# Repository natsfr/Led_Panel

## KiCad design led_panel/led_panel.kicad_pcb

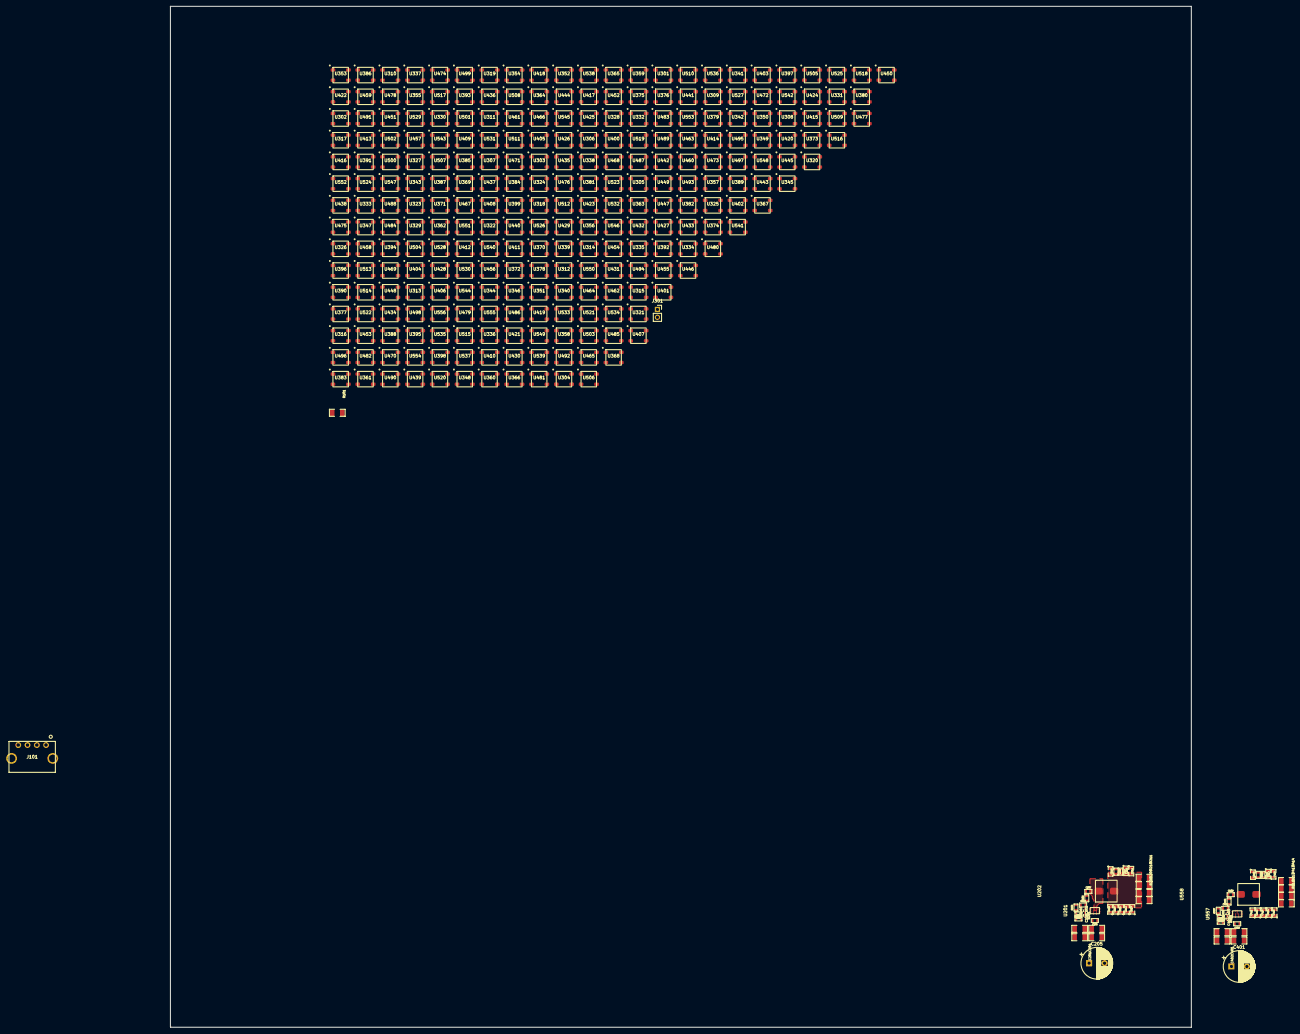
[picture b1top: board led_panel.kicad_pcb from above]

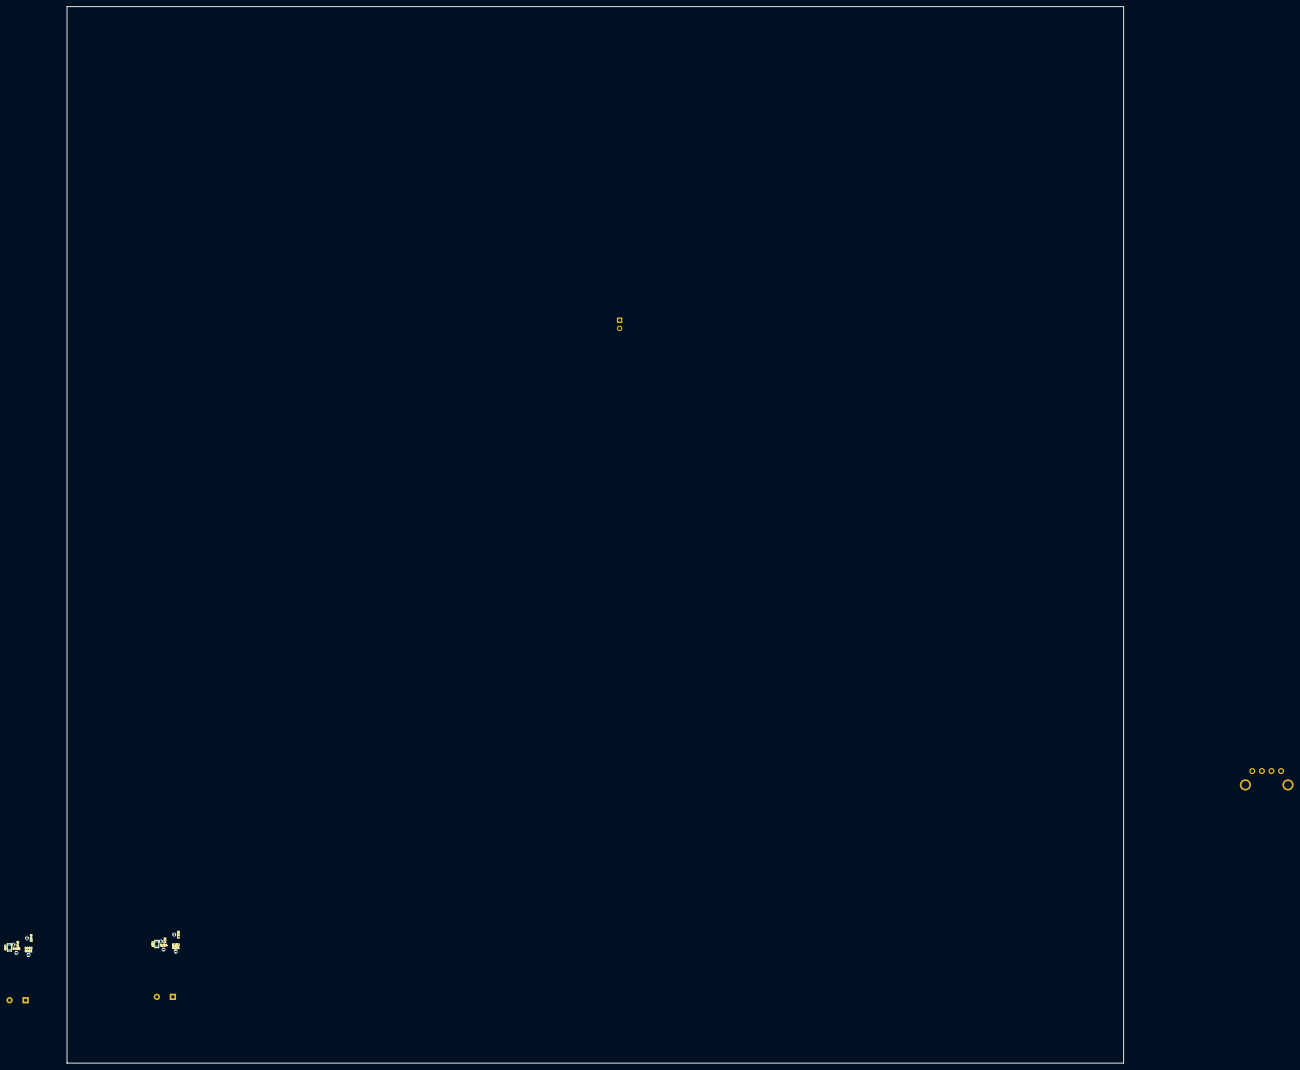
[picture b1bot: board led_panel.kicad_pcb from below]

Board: 4 copper layers, 330.0 x 330.0 mm, 331 parts (12 on the bottom side), 296 nets, no tracks yet.

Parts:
C201, C202, C203, C204, C402, C403, C404, C405: 10uF - 50V; SM1206
C205, C401: 100uF; CP_Radial_D10.0mm_P5.00mm
C206, C217, C218, C220, C406, C409, C419, C420: 100nF; SM0603
C207, C408: 220nF; SM0603
C208, C410: NC; SM0603
C209, C210, C211, C212, C213, C214, C215, C216, C411, C412, C413, C414, C415, C416, C417, C418: 10uF - 16V; SM0805
C219, C407: 1uF; SM0603
J101: 19V 5A Molex; MICROFIT_4POS_FEM_43650-0404
J301: DEBUG_OUT; PinSocket_1x02_P2.54mm_Vertical
R101: RES_1206; SM1206
R201, R401: 1.5M; SM0402
R202, R212, R213, R402, R403, R404: NC; SM0402
R203, R409: 9.53k; SM0402
R204, R410: 43k; SM0402
R205, R405: 3.3; SM0603
R206, R207, R407, R408: NC; SM0603
R208, R209, R210, R211, R411, R412, R413, R414: 0; SM1206
R214, R406: 100k; SM0402
U201, U557: MP8759GD; MP8759_QFN12
U202, U558: IND_SMALL; WE-HCI_7x7x3.8mm
U301, U302, U303, U304, U305, U306, U307, U308, U309, U310, U311, U312, U313, U314, U315, U316, U317, U318, U319, U320, U321, U322, U323, U324, U325, U326, U327, U328, U329, U330, U331, U332, U333, U334, U335, U336, U337, U338, U339, U340, U341, U342, U343, U344, U345, U346, U347, U348, U349, U350, U351, U352, U353, U354, U355, U356, U357, U358, U359, U360, U361, U362, U363, U364, U365, U366, U367, U368, U369, U370, U371, U372, U373, U374, U375, U376, U377, U378, U379, U380, U381, U382, U383, U384, U385, U386, U387, U388, U389, U390, U391, U392, U393, U394, U395, U396, U397, U398, U399, U400, U401, U402, U403, U404, U405, U406, U407, U408, U409, U410, U411, U412, U413, U414, U415, U416, U417, U418, U419, U420, U421, U422, U423, U424, U425, U426, U427, U428, U429, U430, U431, U432, U433, U434, U435, U436, U437, U438, U439, U440, U441, U442, U443, U444, U445, U446, U447, U448, U449, U450, U451, U452, U453, U454, U455, U456, U457, U458, U459, U460, U461, U462, U463, U464, U465, U466, U467, U468, U469, U470, U471, U472, U473, U474, U475, U476, U477, U478, U479, U480, U481, U482, U483, U484, U485, U486, U487, U488, U489, U490, U491, U492, U493, U494, U495, U496, U497, U498, U499, U500, U501, U502, U503, U504, U505, U506, U507, U508, U509, U510, U511, U512, U513, U514, U515, U516, U517, U518, U519, U520, U521, U522, U523, U524, U525, U526, U527, U528, U529, U530, U531, U532, U533, U534, U535, U536, U537, U538, U539, U540, U541, U542, U543, U544, U545, U546, U547, U548, U549, U550, U551, U552, U553, U554, U555, U556: WS2812B; WS2812B_50x50

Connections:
/Lane 0/LANE_POWER: R101.2, U301.1 (VDD), U309.1 (VDD), U317.1 (VDD), U325.1 (VDD), U333.1 (VDD), U341.1 (VDD), U349.1 (VDD), U357.1 (VDD), U365.1 (VDD), U373.1 (VDD), U381.1 (VDD), U389.1 (VDD), U397.1 (VDD), U405.1 (VDD), U413.1 (VDD), U421.1 (VDD)
/Power Lane 0/19V: C201.2, C202.2, C203.2, C204.2, C205.2, C206.2, C401.2, C402.2, C403.2, C404.2, C405.2, C406.2, J101.3, J101.4, U201.1 (Vin), U557.1 (Vin)
/Power Lane 0/PG: R214.2, U201.3 (PG)
/Power Lane 0/POUT_SW: C208.2, C209.2, C210.2, C211.2, C212.2, C213.2, C214.2, C215.2, C216.2, C217.2, C218.2, C220.2, R204.1, R208.1, R209.1, R210.1, R211.1, U201.5 (Vout), U202.2
/Power Lane 0/POWER_OUT: R101.1, R208.2, R209.2, R210.2, R211.2
/Power Lane 0/SW: C207.2, R206.2, U201.7 (SW), U202.1
/Power Lane 1/PG: R406.2, U557.3 (PG)
/Power Lane 1/POUT_SW: C409.2, C410.2, C411.2, C412.2, C413.2, C414.2, C415.2, C416.2, C417.2, C418.2, C419.2, C420.2, R410.1, R411.1, R412.1, R413.1, R414.1, U557.5 (Vout), U558.2
/Power Lane 1/POWER_OUT: R411.2, R412.2, R413.2, R414.2
/Power Lane 1/SW: C408.2, R407.2, U557.7 (SW), U558.1
GND: C201.1, C202.1, C203.1, C204.1, C205.1, C206.1, C209.1, C210.1, C211.1, C212.1, C213.1, C214.1, C215.1, C216.1, C217.1, C218.1, C219.1, C220.1, C401.1, C402.1, C403.1, C404.1, C405.1, C406.1, C407.1, C409.1, C411.1, C412.1, C413.1, C414.1, C415.1, C416.1, C417.1, C418.1, C419.1, C420.1, J101.1, J101.2, J301.1, R202.1, R203.1, R213.1, R402.1, R404.1, R409.1, U201.2 (PGND), U201.10 (AGND), U301.3 (VSS), U302.3 (VSS), U303.3 (VSS), U304.3 (VSS), U305.3 (VSS), U306.3 (VSS), U307.3 (VSS), U308.3 (VSS), U309.3 (VSS), U310.3 (VSS), U311.3 (VSS), U312.3 (VSS), U313.3 (VSS), U314.3 (VSS), U315.3 (VSS), U316.3 (VSS), U317.3 (VSS), U318.3 (VSS), U319.3 (VSS), U320.3 (VSS), U321.3 (VSS), U322.3 (VSS), U323.3 (VSS), U324.3 (VSS), U325.3 (VSS), U326.3 (VSS), U327.3 (VSS), U328.3 (VSS), U329.3 (VSS), U330.3 (VSS), U331.3 (VSS), U332.3 (VSS), U333.3 (VSS), U334.3 (VSS), U335.3 (VSS), U336.3 (VSS), U337.3 (VSS), U338.3 (VSS), U339.3 (VSS), U340.3 (VSS), U341.3 (VSS), U342.3 (VSS), U343.3 (VSS), U344.3 (VSS), U345.3 (VSS), U346.3 (VSS), U347.3 (VSS), U348.3 (VSS), U349.3 (VSS), U350.3 (VSS), U351.3 (VSS), U352.3 (VSS), U353.3 (VSS), U354.3 (VSS), U355.3 (VSS), U356.3 (VSS), U357.3 (VSS), U358.3 (VSS), U359.3 (VSS), U360.3 (VSS), U361.3 (VSS), U362.3 (VSS), U363.3 (VSS), U364.3 (VSS), U365.3 (VSS), U366.3 (VSS), U367.3 (VSS), U368.3 (VSS), U369.3 (VSS), U370.3 (VSS), U371.3 (VSS), U372.3 (VSS), U373.3 (VSS), U374.3 (VSS), U375.3 (VSS), U376.3 (VSS), U377.3 (VSS), U378.3 (VSS), U379.3 (VSS), U380.3 (VSS), U381.3 (VSS), U382.3 (VSS), U383.3 (VSS), U384.3 (VSS), U385.3 (VSS), U386.3 (VSS), U387.3 (VSS), U388.3 (VSS), U389.3 (VSS), U390.3 (VSS), U391.3 (VSS), U392.3 (VSS), U393.3 (VSS), U394.3 (VSS), U395.3 (VSS), U396.3 (VSS), U397.3 (VSS), U398.3 (VSS), U399.3 (VSS), U400.3 (VSS), U401.3 (VSS), U402.3 (VSS), U403.3 (VSS), U404.3 (VSS), U405.3 (VSS), U406.3 (VSS), U407.3 (VSS), U408.3 (VSS), U409.3 (VSS), U410.3 (VSS), U411.3 (VSS), U412.3 (VSS), U413.3 (VSS), U414.3 (VSS), U415.3 (VSS), U416.3 (VSS), U417.3 (VSS), U418.3 (VSS), U419.3 (VSS), U420.3 (VSS), U421.3 (VSS), U422.3 (VSS), U423.3 (VSS), U424.3 (VSS), U425.3 (VSS), U426.3 (VSS), U427.3 (VSS), U428.3 (VSS), U429.3 (VSS), U430.3 (VSS), U431.3 (VSS), U432.3 (VSS), U433.3 (VSS), U434.3 (VSS), U435.3 (VSS), U436.3 (VSS), U437.3 (VSS), U438.3 (VSS), U439.3 (VSS), U440.3 (VSS), U441.3 (VSS), U442.3 (VSS), U443.3 (VSS), U444.3 (VSS), U445.3 (VSS), U446.3 (VSS), U447.3 (VSS), U448.3 (VSS), U449.3 (VSS), U450.3 (VSS), U451.3 (VSS), U452.3 (VSS), U453.3 (VSS), U454.3 (VSS), U455.3 (VSS), U456.3 (VSS), U457.3 (VSS), U458.3 (VSS), U459.3 (VSS), U460.3 (VSS), U461.3 (VSS), U462.3 (VSS), U463.3 (VSS), U464.3 (VSS), U465.3 (VSS), U466.3 (VSS), U467.3 (VSS), U468.3 (VSS), U469.3 (VSS), U470.3 (VSS), U471.3 (VSS), U472.3 (VSS), U473.3 (VSS), U474.3 (VSS), U475.3 (VSS), U476.3 (VSS), U477.3 (VSS), U478.3 (VSS), U479.3 (VSS), U480.3 (VSS), U481.3 (VSS), U482.3 (VSS), U483.3 (VSS), U484.3 (VSS), U485.3 (VSS), U486.3 (VSS), U487.3 (VSS), U488.3 (VSS), U489.3 (VSS), U490.3 (VSS), U491.3 (VSS), U492.3 (VSS), U493.3 (VSS), U494.3 (VSS), U495.3 (VSS), U496.3 (VSS), U497.3 (VSS), U498.3 (VSS), U499.3 (VSS), U500.3 (VSS), U501.3 (VSS), U502.3 (VSS), U503.3 (VSS), U504.3 (VSS), U505.3 (VSS), U506.3 (VSS), U507.3 (VSS), U508.3 (VSS), U509.3 (VSS), U510.3 (VSS), U511.3 (VSS), U512.3 (VSS), U513.3 (VSS), U514.3 (VSS), U515.3 (VSS), U516.3 (VSS), U517.3 (VSS), U518.3 (VSS), U519.3 (VSS), U520.3 (VSS), U521.3 (VSS), U522.3 (VSS), U523.3 (VSS), U524.3 (VSS), U525.3 (VSS), U526.3 (VSS), U527.3 (VSS), U528.3 (VSS), U529.3 (VSS), U530.3 (VSS), U531.3 (VSS), U532.3 (VSS), U533.3 (VSS), U534.3 (VSS), U535.3 (VSS), U536.3 (VSS), U537.3 (VSS), U538.3 (VSS), U539.3 (VSS), U540.3 (VSS), U541.3 (VSS), U542.3 (VSS), U543.3 (VSS), U544.3 (VSS), U545.3 (VSS), U546.3 (VSS), U547.3 (VSS), U548.3 (VSS), U549.3 (VSS), U550.3 (VSS), U551.3 (VSS), U552.3 (VSS), U553.3 (VSS), U554.3 (VSS), U555.3 (VSS), U556.3 (VSS), U557.2 (PGND), U557.10 (AGND)
unnamed: C207.1, R205.2
unnamed: C208.1, R206.1, R207.2
unnamed: C407.2, R403.1, R406.1, U557.9 (Vcc)
unnamed: C408.1, R405.2
unnamed: C410.1, R407.1, R408.2
unnamed: J301.2, U556.2 (DOUT)
unnamed: R201.2, R202.2, U201.12 (EN)
unnamed: R203.2, R204.2, R207.1, U201.11 (FB)
unnamed: R205.1, U201.8 (BST)
unnamed: R401.2, R402.2, U557.12 (EN)
unnamed: R403.2, R404.2, U557.6 (MODE)
unnamed: R405.1, U557.8 (BST)
unnamed: R408.1, R409.2, R410.2, U557.11 (FB)
unnamed: R212.2, R213.2, U201.6 (MODE)
unnamed: C219.2, R212.1, R214.1, U201.9 (Vcc)
unnamed: U301.2 (DOUT), U422.4 (DIN)
unnamed: U301.4 (DIN), U309.2 (DOUT)
unnamed: U302.1 (VDD), U310.1 (VDD), U318.1 (VDD), U326.1 (VDD), U334.1 (VDD), U342.1 (VDD), U350.1 (VDD), U358.1 (VDD), U366.1 (VDD), U374.1 (VDD), U382.1 (VDD), U390.1 (VDD), U398.1 (VDD), U406.1 (VDD), U414.1 (VDD), U422.1 (VDD)
unnamed: U302.2 (DOUT), U423.4 (DIN)
unnamed: U302.4 (DIN), U310.2 (DOUT)
unnamed: U303.1 (VDD), U311.1 (VDD), U319.1 (VDD), U327.1 (VDD), U335.1 (VDD), U343.1 (VDD), U351.1 (VDD), U359.1 (VDD), U367.1 (VDD), U375.1 (VDD), U383.1 (VDD), U391.1 (VDD), U399.1 (VDD), U407.1 (VDD), U415.1 (VDD), U423.1 (VDD)
unnamed: U303.2 (DOUT), U424.4 (DIN)
unnamed: U303.4 (DIN), U311.2 (DOUT)
unnamed: U304.1 (VDD), U312.1 (VDD), U320.1 (VDD), U328.1 (VDD), U336.1 (VDD), U344.1 (VDD), U352.1 (VDD), U360.1 (VDD), U368.1 (VDD), U376.1 (VDD), U384.1 (VDD), U392.1 (VDD), U400.1 (VDD), U408.1 (VDD), U416.1 (VDD), U424.1 (VDD)
unnamed: U304.2 (DOUT), U425.4 (DIN)
unnamed: U304.4 (DIN), U312.2 (DOUT)
unnamed: U305.1 (VDD), U313.1 (VDD), U321.1 (VDD), U329.1 (VDD), U337.1 (VDD), U345.1 (VDD), U353.1 (VDD), U361.1 (VDD), U369.1 (VDD), U377.1 (VDD), U385.1 (VDD), U393.1 (VDD), U401.1 (VDD), U409.1 (VDD), U417.1 (VDD), U425.1 (VDD)
unnamed: U305.2 (DOUT), U426.4 (DIN)
unnamed: U305.4 (DIN), U313.2 (DOUT)
unnamed: U306.1 (VDD), U314.1 (VDD), U322.1 (VDD), U330.1 (VDD), U338.1 (VDD), U346.1 (VDD), U354.1 (VDD), U362.1 (VDD), U370.1 (VDD), U378.1 (VDD), U386.1 (VDD), U394.1 (VDD), U402.1 (VDD), U410.1 (VDD), U418.1 (VDD), U426.1 (VDD)
unnamed: U306.2 (DOUT), U427.4 (DIN)
unnamed: U306.4 (DIN), U314.2 (DOUT)
unnamed: U307.1 (VDD), U315.1 (VDD), U323.1 (VDD), U331.1 (VDD), U339.1 (VDD), U347.1 (VDD), U355.1 (VDD), U363.1 (VDD), U371.1 (VDD), U379.1 (VDD), U387.1 (VDD), U395.1 (VDD), U403.1 (VDD), U411.1 (VDD), U419.1 (VDD), U427.1 (VDD)
unnamed: U307.2 (DOUT), U428.4 (DIN)
unnamed: U307.4 (DIN), U315.2 (DOUT)
unnamed: U308.1 (VDD), U316.1 (VDD), U324.1 (VDD), U332.1 (VDD), U340.1 (VDD), U348.1 (VDD), U356.1 (VDD), U364.1 (VDD), U372.1 (VDD), U380.1 (VDD), U388.1 (VDD), U396.1 (VDD), U404.1 (VDD), U412.1 (VDD), U420.1 (VDD), U428.1 (VDD)
unnamed: U308.2 (DOUT), U429.4 (DIN)
unnamed: U308.4 (DIN), U316.2 (DOUT)
unnamed: U309.4 (DIN), U317.2 (DOUT)
unnamed: U310.4 (DIN), U318.2 (DOUT)
unnamed: U311.4 (DIN), U319.2 (DOUT)
unnamed: U312.4 (DIN), U320.2 (DOUT)
unnamed: U313.4 (DIN), U321.2 (DOUT)
unnamed: U314.4 (DIN), U322.2 (DOUT)
unnamed: U315.4 (DIN), U323.2 (DOUT)
unnamed: U316.4 (DIN), U324.2 (DOUT)
unnamed: U317.4 (DIN), U325.2 (DOUT)
unnamed: U318.4 (DIN), U326.2 (DOUT)
unnamed: U319.4 (DIN), U327.2 (DOUT)
unnamed: U320.4 (DIN), U328.2 (DOUT)
unnamed: U321.4 (DIN), U329.2 (DOUT)
unnamed: U322.4 (DIN), U330.2 (DOUT)
unnamed: U323.4 (DIN), U331.2 (DOUT)
unnamed: U324.4 (DIN), U332.2 (DOUT)
unnamed: U325.4 (DIN), U333.2 (DOUT)
unnamed: U326.4 (DIN), U334.2 (DOUT)
unnamed: U327.4 (DIN), U335.2 (DOUT)
unnamed: U328.4 (DIN), U336.2 (DOUT)
unnamed: U329.4 (DIN), U337.2 (DOUT)
unnamed: U330.4 (DIN), U338.2 (DOUT)
unnamed: U331.4 (DIN), U339.2 (DOUT)
unnamed: U332.4 (DIN), U340.2 (DOUT)
unnamed: U333.4 (DIN), U341.2 (DOUT)
unnamed: U334.4 (DIN), U342.2 (DOUT)
unnamed: U335.4 (DIN), U343.2 (DOUT)
unnamed: U336.4 (DIN), U344.2 (DOUT)
unnamed: U337.4 (DIN), U345.2 (DOUT)
unnamed: U338.4 (DIN), U346.2 (DOUT)
unnamed: U339.4 (DIN), U347.2 (DOUT)
unnamed: U340.4 (DIN), U348.2 (DOUT)
unnamed: U341.4 (DIN), U349.2 (DOUT)
unnamed: U342.4 (DIN), U350.2 (DOUT)
unnamed: U343.4 (DIN), U351.2 (DOUT)
unnamed: U344.4 (DIN), U352.2 (DOUT)
unnamed: U345.4 (DIN), U353.2 (DOUT)
unnamed: U346.4 (DIN), U354.2 (DOUT)
unnamed: U347.4 (DIN), U355.2 (DOUT)
unnamed: U348.4 (DIN), U356.2 (DOUT)
unnamed: U349.4 (DIN), U357.2 (DOUT)
unnamed: U350.4 (DIN), U358.2 (DOUT)
unnamed: U351.4 (DIN), U359.2 (DOUT)
unnamed: U352.4 (DIN), U360.2 (DOUT)
unnamed: U353.4 (DIN), U361.2 (DOUT)
unnamed: U354.4 (DIN), U362.2 (DOUT)
unnamed: U355.4 (DIN), U363.2 (DOUT)
unnamed: U356.4 (DIN), U364.2 (DOUT)
unnamed: U357.4 (DIN), U365.2 (DOUT)
unnamed: U358.4 (DIN), U366.2 (DOUT)
unnamed: U359.4 (DIN), U367.2 (DOUT)
unnamed: U360.4 (DIN), U368.2 (DOUT)
unnamed: U361.4 (DIN), U369.2 (DOUT)
unnamed: U362.4 (DIN), U370.2 (DOUT)
unnamed: U363.4 (DIN), U371.2 (DOUT)
unnamed: U364.4 (DIN), U372.2 (DOUT)
unnamed: U365.4 (DIN), U373.2 (DOUT)
unnamed: U366.4 (DIN), U374.2 (DOUT)
unnamed: U367.4 (DIN), U375.2 (DOUT)
unnamed: U368.4 (DIN), U376.2 (DOUT)
unnamed: U369.4 (DIN), U377.2 (DOUT)
unnamed: U370.4 (DIN), U378.2 (DOUT)
unnamed: U371.4 (DIN), U379.2 (DOUT)
unnamed: U372.4 (DIN), U380.2 (DOUT)
unnamed: U373.4 (DIN), U381.2 (DOUT)
unnamed: U374.4 (DIN), U382.2 (DOUT)
unnamed: U375.4 (DIN), U383.2 (DOUT)
unnamed: U376.4 (DIN), U384.2 (DOUT)
unnamed: U377.4 (DIN), U385.2 (DOUT)
unnamed: U378.4 (DIN), U386.2 (DOUT)
unnamed: U379.4 (DIN), U387.2 (DOUT)
unnamed: U380.4 (DIN), U388.2 (DOUT)
unnamed: U381.4 (DIN), U389.2 (DOUT)
unnamed: U382.4 (DIN), U390.2 (DOUT)
unnamed: U383.4 (DIN), U391.2 (DOUT)
unnamed: U384.4 (DIN), U392.2 (DOUT)
unnamed: U385.4 (DIN), U393.2 (DOUT)
unnamed: U386.4 (DIN), U394.2 (DOUT)
unnamed: U387.4 (DIN), U395.2 (DOUT)
unnamed: U388.4 (DIN), U396.2 (DOUT)
unnamed: U389.4 (DIN), U397.2 (DOUT)
unnamed: U390.4 (DIN), U398.2 (DOUT)
unnamed: U391.4 (DIN), U399.2 (DOUT)
unnamed: U392.4 (DIN), U400.2 (DOUT)
unnamed: U393.4 (DIN), U401.2 (DOUT)
unnamed: U394.4 (DIN), U402.2 (DOUT)
unnamed: U395.4 (DIN), U403.2 (DOUT)
unnamed: U396.4 (DIN), U404.2 (DOUT)
unnamed: U397.4 (DIN), U405.2 (DOUT)
unnamed: U398.4 (DIN), U406.2 (DOUT)
unnamed: U399.4 (DIN), U407.2 (DOUT)
unnamed: U400.4 (DIN), U408.2 (DOUT)
unnamed: U401.4 (DIN), U409.2 (DOUT)
unnamed: U402.4 (DIN), U410.2 (DOUT)
unnamed: U403.4 (DIN), U411.2 (DOUT)
unnamed: U404.4 (DIN), U412.2 (DOUT)
unnamed: U405.4 (DIN), U413.2 (DOUT)
unnamed: U406.4 (DIN), U414.2 (DOUT)
unnamed: U407.4 (DIN), U415.2 (DOUT)
unnamed: U408.4 (DIN), U416.2 (DOUT)
unnamed: U409.4 (DIN), U417.2 (DOUT)
unnamed: U410.4 (DIN), U418.2 (DOUT)
unnamed: U411.4 (DIN), U419.2 (DOUT)
unnamed: U412.4 (DIN), U420.2 (DOUT)
unnamed: U413.4 (DIN), U421.2 (DOUT)
unnamed: U414.4 (DIN), U422.2 (DOUT)
unnamed: U415.4 (DIN), U423.2 (DOUT)
unnamed: U416.4 (DIN), U424.2 (DOUT)
unnamed: U417.4 (DIN), U425.2 (DOUT)
unnamed: U418.4 (DIN), U426.2 (DOUT)
unnamed: U419.4 (DIN), U427.2 (DOUT)
unnamed: U420.4 (DIN), U428.2 (DOUT)
unnamed: U429.1 (VDD), U430.1 (VDD), U431.1 (VDD), U432.1 (VDD), U433.1 (VDD), U434.1 (VDD), U435.1 (VDD), U436.1 (VDD), U437.1 (VDD), U438.1 (VDD), U439.1 (VDD), U440.1 (VDD), U441.1 (VDD), U442.1 (VDD), U443.1 (VDD), U444.1 (VDD)
unnamed: U429.2 (DOUT), U430.4 (DIN)
unnamed: U430.2 (DOUT), U431.4 (DIN)
unnamed: U431.2 (DOUT), U432.4 (DIN)
unnamed: U432.2 (DOUT), U433.4 (DIN)
unnamed: U433.2 (DOUT), U434.4 (DIN)
unnamed: U434.2 (DOUT), U435.4 (DIN)
unnamed: U435.2 (DOUT), U436.4 (DIN)
unnamed: U436.2 (DOUT), U437.4 (DIN)
unnamed: U437.2 (DOUT), U438.4 (DIN)
unnamed: U438.2 (DOUT), U439.4 (DIN)
unnamed: U439.2 (DOUT), U440.4 (DIN)
unnamed: U440.2 (DOUT), U441.4 (DIN)
unnamed: U441.2 (DOUT), U442.4 (DIN)
unnamed: U442.2 (DOUT), U443.4 (DIN)
unnamed: U443.2 (DOUT), U444.4 (DIN)
unnamed: U444.2 (DOUT), U445.4 (DIN)
unnamed: U445.1 (VDD), U446.1 (VDD), U447.1 (VDD), U448.1 (VDD), U449.1 (VDD), U450.1 (VDD), U451.1 (VDD), U452.1 (VDD), U453.1 (VDD), U454.1 (VDD), U455.1 (VDD), U456.1 (VDD), U457.1 (VDD), U458.1 (VDD), U459.1 (VDD), U460.1 (VDD)
unnamed: U445.2 (DOUT), U446.4 (DIN)
unnamed: U446.2 (DOUT), U447.4 (DIN)
unnamed: U447.2 (DOUT), U448.4 (DIN)
unnamed: U448.2 (DOUT), U449.4 (DIN)
unnamed: U449.2 (DOUT), U450.4 (DIN)
unnamed: U450.2 (DOUT), U451.4 (DIN)
unnamed: U451.2 (DOUT), U452.4 (DIN)
unnamed: U452.2 (DOUT), U453.4 (DIN)
unnamed: U453.2 (DOUT), U454.4 (DIN)
unnamed: U454.2 (DOUT), U455.4 (DIN)
unnamed: U455.2 (DOUT), U456.4 (DIN)
unnamed: U456.2 (DOUT), U457.4 (DIN)
unnamed: U457.2 (DOUT), U458.4 (DIN)
unnamed: U458.2 (DOUT), U459.4 (DIN)
unnamed: U459.2 (DOUT), U460.4 (DIN)
unnamed: U460.2 (DOUT), U461.4 (DIN)
unnamed: U461.1 (VDD), U462.1 (VDD), U463.1 (VDD), U464.1 (VDD), U465.1 (VDD), U466.1 (VDD), U467.1 (VDD), U468.1 (VDD), U469.1 (VDD), U470.1 (VDD), U471.1 (VDD), U472.1 (VDD), U473.1 (VDD), U474.1 (VDD), U475.1 (VDD), U476.1 (VDD)
unnamed: U461.2 (DOUT), U462.4 (DIN)
unnamed: U462.2 (DOUT), U463.4 (DIN)
unnamed: U463.2 (DOUT), U464.4 (DIN)
unnamed: U464.2 (DOUT), U465.4 (DIN)
unnamed: U465.2 (DOUT), U466.4 (DIN)
unnamed: U466.2 (DOUT), U467.4 (DIN)
unnamed: U467.2 (DOUT), U468.4 (DIN)
unnamed: U468.2 (DOUT), U469.4 (DIN)
unnamed: U469.2 (DOUT), U470.4 (DIN)
unnamed: U470.2 (DOUT), U471.4 (DIN)
unnamed: U471.2 (DOUT), U472.4 (DIN)
unnamed: U472.2 (DOUT), U473.4 (DIN)
unnamed: U473.2 (DOUT), U474.4 (DIN)
unnamed: U474.2 (DOUT), U475.4 (DIN)
unnamed: U475.2 (DOUT), U476.4 (DIN)
unnamed: U476.2 (DOUT), U477.4 (DIN)
unnamed: U477.1 (VDD), U478.1 (VDD), U479.1 (VDD), U480.1 (VDD), U481.1 (VDD), U482.1 (VDD), U483.1 (VDD), U484.1 (VDD), U485.1 (VDD), U486.1 (VDD), U487.1 (VDD), U488.1 (VDD), U489.1 (VDD), U490.1 (VDD), U491.1 (VDD), U492.1 (VDD)
unnamed: U477.2 (DOUT), U478.4 (DIN)
unnamed: U478.2 (DOUT), U479.4 (DIN)
unnamed: U479.2 (DOUT), U480.4 (DIN)
unnamed: U480.2 (DOUT), U481.4 (DIN)
unnamed: U481.2 (DOUT), U482.4 (DIN)
unnamed: U482.2 (DOUT), U483.4 (DIN)
unnamed: U483.2 (DOUT), U484.4 (DIN)
unnamed: U484.2 (DOUT), U485.4 (DIN)
unnamed: U485.2 (DOUT), U486.4 (DIN)
unnamed: U486.2 (DOUT), U487.4 (DIN)
unnamed: U487.2 (DOUT), U488.4 (DIN)
unnamed: U488.2 (DOUT), U489.4 (DIN)
unnamed: U489.2 (DOUT), U490.4 (DIN)
unnamed: U490.2 (DOUT), U491.4 (DIN)
unnamed: U491.2 (DOUT), U492.4 (DIN)
unnamed: U492.2 (DOUT), U493.4 (DIN)
unnamed: U493.1 (VDD), U494.1 (VDD), U495.1 (VDD), U496.1 (VDD), U497.1 (VDD), U498.1 (VDD), U499.1 (VDD), U500.1 (VDD), U501.1 (VDD), U502.1 (VDD), U503.1 (VDD), U504.1 (VDD), U505.1 (VDD), U506.1 (VDD), U507.1 (VDD), U508.1 (VDD)
unnamed: U493.2 (DOUT), U494.4 (DIN)
unnamed: U494.2 (DOUT), U495.4 (DIN)
unnamed: U495.2 (DOUT), U496.4 (DIN)
unnamed: U496.2 (DOUT), U497.4 (DIN)
unnamed: U497.2 (DOUT), U498.4 (DIN)
unnamed: U498.2 (DOUT), U499.4 (DIN)
unnamed: U499.2 (DOUT), U500.4 (DIN)
unnamed: U500.2 (DOUT), U501.4 (DIN)
unnamed: U501.2 (DOUT), U502.4 (DIN)
unnamed: U502.2 (DOUT), U503.4 (DIN)
unnamed: U503.2 (DOUT), U504.4 (DIN)
unnamed: U504.2 (DOUT), U505.4 (DIN)
unnamed: U505.2 (DOUT), U506.4 (DIN)
unnamed: U506.2 (DOUT), U507.4 (DIN)
unnamed: U507.2 (DOUT), U508.4 (DIN)
unnamed: U508.2 (DOUT), U509.4 (DIN)
unnamed: U509.1 (VDD), U510.1 (VDD), U511.1 (VDD), U512.1 (VDD), U513.1 (VDD), U514.1 (VDD), U515.1 (VDD), U516.1 (VDD), U517.1 (VDD), U518.1 (VDD), U519.1 (VDD), U520.1 (VDD), U521.1 (VDD), U522.1 (VDD), U523.1 (VDD), U524.1 (VDD)
unnamed: U509.2 (DOUT), U510.4 (DIN)
unnamed: U510.2 (DOUT), U511.4 (DIN)
unnamed: U511.2 (DOUT), U512.4 (DIN)
unnamed: U512.2 (DOUT), U513.4 (DIN)
unnamed: U513.2 (DOUT), U514.4 (DIN)
unnamed: U514.2 (DOUT), U515.4 (DIN)
unnamed: U515.2 (DOUT), U516.4 (DIN)
unnamed: U516.2 (DOUT), U517.4 (DIN)
unnamed: U517.2 (DOUT), U518.4 (DIN)
unnamed: U518.2 (DOUT), U519.4 (DIN)
unnamed: U519.2 (DOUT), U520.4 (DIN)
unnamed: U520.2 (DOUT), U521.4 (DIN)
unnamed: U521.2 (DOUT), U522.4 (DIN)
unnamed: U522.2 (DOUT), U523.4 (DIN)
unnamed: U523.2 (DOUT), U524.4 (DIN)
unnamed: U524.2 (DOUT), U525.4 (DIN)
unnamed: U525.1 (VDD), U526.1 (VDD), U527.1 (VDD), U528.1 (VDD), U529.1 (VDD), U530.1 (VDD), U531.1 (VDD), U532.1 (VDD), U533.1 (VDD), U534.1 (VDD), U535.1 (VDD), U536.1 (VDD), U537.1 (VDD), U538.1 (VDD), U539.1 (VDD), U540.1 (VDD)
unnamed: U525.2 (DOUT), U526.4 (DIN)
unnamed: U526.2 (DOUT), U527.4 (DIN)
unnamed: U527.2 (DOUT), U528.4 (DIN)
unnamed: U528.2 (DOUT), U529.4 (DIN)
unnamed: U529.2 (DOUT), U530.4 (DIN)
unnamed: U530.2 (DOUT), U531.4 (DIN)
unnamed: U531.2 (DOUT), U532.4 (DIN)
unnamed: U532.2 (DOUT), U533.4 (DIN)
unnamed: U533.2 (DOUT), U534.4 (DIN)
unnamed: U534.2 (DOUT), U535.4 (DIN)
unnamed: U535.2 (DOUT), U536.4 (DIN)
unnamed: U536.2 (DOUT), U537.4 (DIN)
unnamed: U537.2 (DOUT), U538.4 (DIN)
unnamed: U538.2 (DOUT), U539.4 (DIN)
unnamed: U539.2 (DOUT), U540.4 (DIN)
unnamed: U540.2 (DOUT), U541.4 (DIN)
unnamed: U541.1 (VDD), U542.1 (VDD), U543.1 (VDD), U544.1 (VDD), U545.1 (VDD), U546.1 (VDD), U547.1 (VDD), U548.1 (VDD), U549.1 (VDD), U550.1 (VDD), U551.1 (VDD), U552.1 (VDD), U553.1 (VDD), U554.1 (VDD), U555.1 (VDD), U556.1 (VDD)
unnamed: U541.2 (DOUT), U542.4 (DIN)
unnamed: U542.2 (DOUT), U543.4 (DIN)
unnamed: U543.2 (DOUT), U544.4 (DIN)
unnamed: U544.2 (DOUT), U545.4 (DIN)
unnamed: U545.2 (DOUT), U546.4 (DIN)
unnamed: U546.2 (DOUT), U547.4 (DIN)
unnamed: U547.2 (DOUT), U548.4 (DIN)
unnamed: U548.2 (DOUT), U549.4 (DIN)
unnamed: U549.2 (DOUT), U550.4 (DIN)
unnamed: U550.2 (DOUT), U551.4 (DIN)
unnamed: U551.2 (DOUT), U552.4 (DIN)
unnamed: U552.2 (DOUT), U553.4 (DIN)
unnamed: U553.2 (DOUT), U554.4 (DIN)
unnamed: U554.2 (DOUT), U555.4 (DIN)
unnamed: U555.2 (DOUT), U556.4 (DIN)

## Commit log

2022-11-18 starting panel schematic and layout
2022-12-05 placing led
